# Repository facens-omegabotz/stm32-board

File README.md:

# stm32f446-board → KiCad Project

PCB design of a development board for the STM32f446 MCU

## Schematics

The PDF can be found [here](STM32-udemy.pdf)

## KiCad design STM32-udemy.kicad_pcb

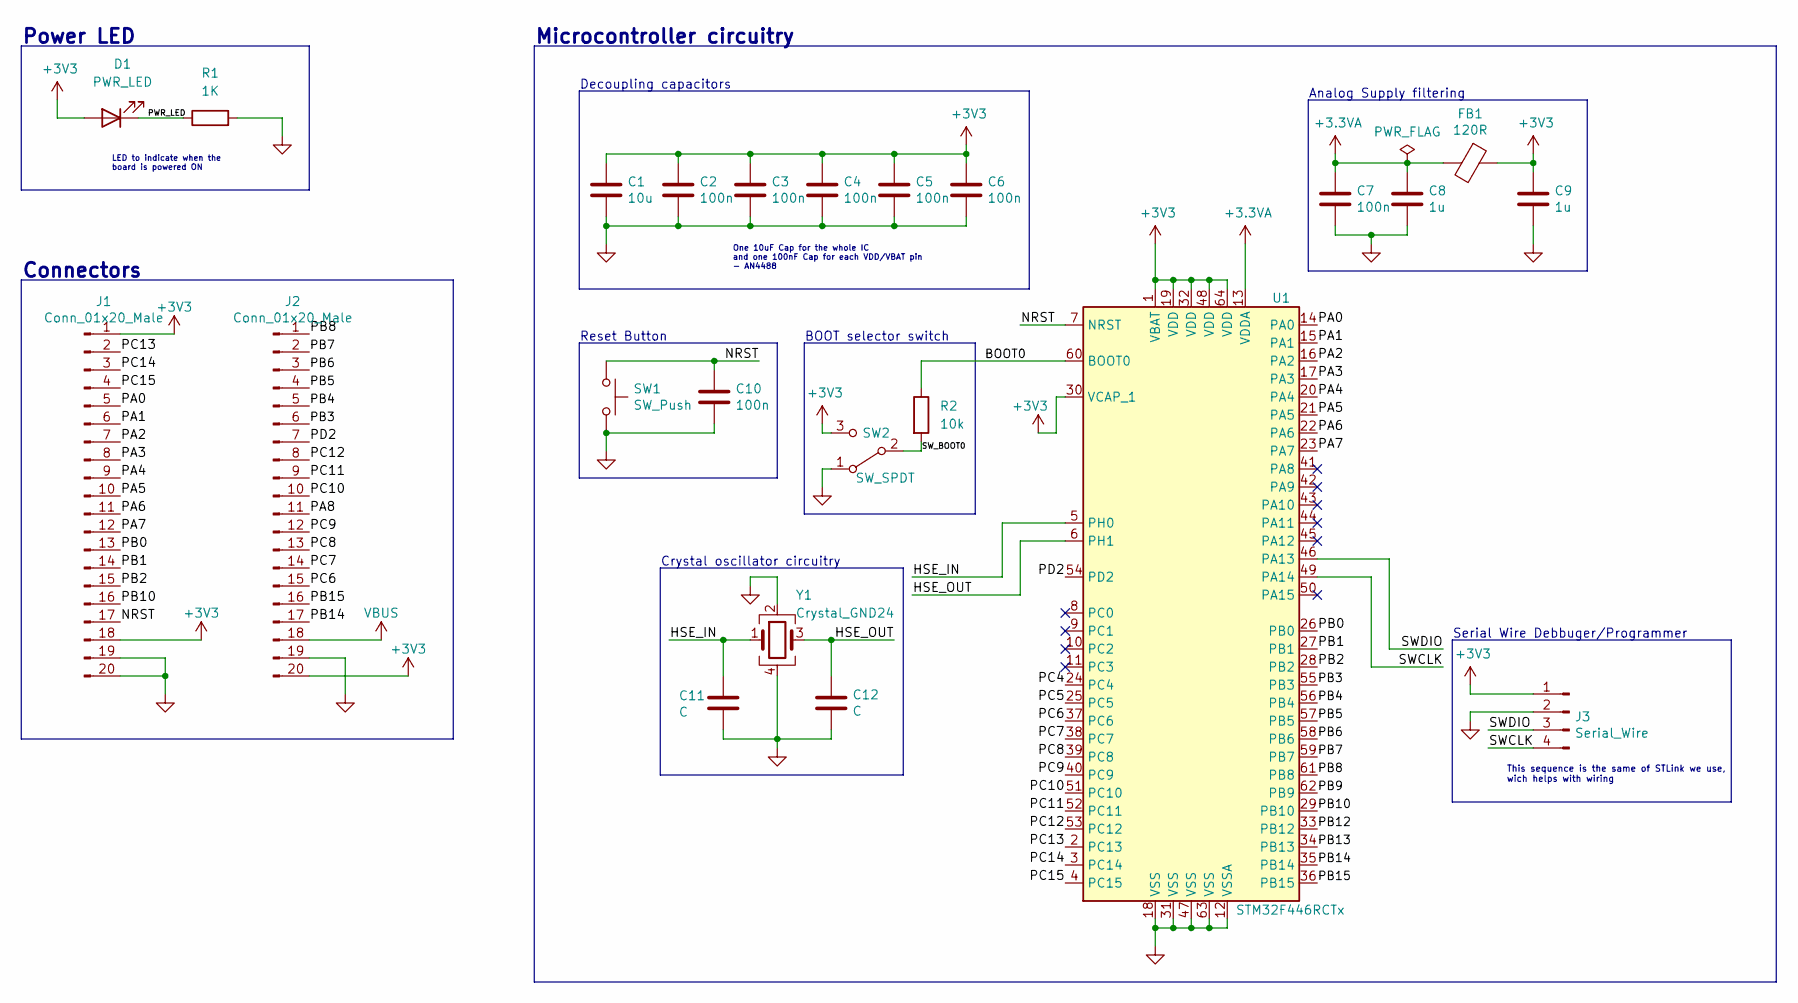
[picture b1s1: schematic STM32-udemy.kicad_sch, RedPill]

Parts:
C1: 10u; C_0805_2012Metric_Pad1.18x1.45mm_HandSolder
C2, C3, C4, C5, C6, C7, C10: 100n; C_0603_1608Metric_Pad1.08x0.95mm_HandSolder
C8, C9: 1u; C_0603_1608Metric_Pad1.08x0.95mm_HandSolder
C11, C12: C; C_0402_1005Metric_Pad0.74x0.62mm_HandSolder
D1: PWR_LED; LED_0603_1608Metric_Pad1.05x0.95mm_HandSolder
FB1: 120R; L_0603_1608Metric_Pad1.05x0.95mm_HandSolder
J1, J2: Conn_01x20_Male; PinHeader_1x20_P2.54mm_Vertical
J3: Serial_Wire; PinHeader_1x04_P2.54mm_Vertical
R1: 1K; R_0603_1608Metric_Pad0.98x0.95mm_HandSolder
R2: 10k; R_0603_1608Metric_Pad0.98x0.95mm_HandSolder
SW1: SW_Push; SW_Push_1P1T_NO_Vertical_Wuerth_434133025816
SW2: SW_SPDT; SW_SPDT_PCM12
U1: STM32F446RCTx; LQFP-64_10x10mm_P0.5mm
Y1: Crystal_GND24; Crystal_SMD_3225-4Pin_3.2x2.5mm

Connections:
+3.3VA: C7.1, C8.1, FB1.2, U1.13 (VDDA)
+3V3: C1.1, C2.1, C3.1, C4.1, C5.1, C6.1, C9.1, D1.2 (A), FB1.1, J1.1, J1.18, J2.20, J3.1, SW2.3 (C), U1.1 (VBAT), U1.19 (VDD), U1.30 (VCAP_1), U1.32 (VDD), U1.48 (VDD), U1.64 (VDD)
/BOOT0: R2.1, U1.60 (BOOT0)
/HSE_IN: C11.1, U1.5 (PH0), Y1.1
/HSE_OUT: C12.1, U1.6 (PH1), Y1.3
/NRST: C10.1, J1.17, SW1.1, U1.7 (NRST)
/PA0: J1.5, U1.14 (PA0)
/PA1: J1.6, U1.15 (PA1)
/PA2: J1.7, U1.16 (PA2)
/PA3: J1.8, U1.17 (PA3)
/PA4: J1.9, U1.20 (PA4)
/PA5: J1.10, U1.21 (PA5)
/PA6: J1.11, U1.22 (PA6)
/PA7: J1.12, U1.23 (PA7)
/PA8: J2.11
/PB0: J1.13, U1.26 (PB0)
/PB1: J1.14, U1.27 (PB1)
/PB2: J1.15, U1.28 (PB2)
/PB3: J2.6, U1.55 (PB3)
/PB4: J2.5, U1.56 (PB4)
/PB5: J2.4, U1.57 (PB5)
/PB6: J2.3, U1.58 (PB6)
/PB7: J2.2, U1.59 (PB7)
/PB8: J2.1, U1.61 (PB8)
/PB9: U1.62 (PB9)
/PB10: J1.16, U1.29 (PB10)
/PB12: U1.33 (PB12)
/PB13: U1.34 (PB13)
/PB14: J2.17, U1.35 (PB14)
/PB15: J2.16, U1.36 (PB15)
/PC4: U1.24 (PC4)
/PC5: U1.25 (PC5)
/PC6: J2.15, U1.37 (PC6)
/PC7: J2.14, U1.38 (PC7)
/PC8: J2.13, U1.39 (PC8)
/PC9: J2.12, U1.40 (PC9)
/PC10: J2.10, U1.51 (PC10)
/PC11: J2.9, U1.52 (PC11)
/PC12: J2.8, U1.53 (PC12)
/PC13: J1.2, U1.2 (PC13)
/PC14: J1.3, U1.3 (PC14)
/PC15: J1.4, U1.4 (PC15)
/PD2: J2.7, U1.54 (PD2)
/PWR_LED: D1.1 (K), R1.1
/SWCLK: J3.4, U1.49 (PA14)
/SWDIO: J3.3, U1.46 (PA13)
/SW_BOOT0: R2.2, SW2.2 (B)
GND: C1.2, C2.2, C3.2, C4.2, C5.2, C6.2, C7.2, C8.2, C9.2, C10.2, C11.2, C12.2, J1.19, J1.20, J2.19, J3.2, R1.2, SW1.2, SW2.1 (A), U1.12 (VSSA), U1.18 (VSS), U1.31 (VSS), U1.47 (VSS), U1.63 (VSS), Y1.2, Y1.4
VBUS: J2.18

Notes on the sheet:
Connectors
Crystal oscillator circuitry
Reset Button
LED to indicate when the board is powered ON
Microcontroller circuitry
This sequence is the same of STLink we use, wich helps with wiring
Power LED
Analog Supply filtering
BOOT selector switch
Serial Wire Debbuger/Programmer
Decoupling capacitors
One 10uF Cap for the whole IC and one 100nF Cap for each VDD/VBAT pin - AN4488

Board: 2 copper layers, 23 parts (12 on the bottom side), 42 nets, no tracks yet.

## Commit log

2022-02-07 Add Schematic file
    First local commit, adding schematic file with:
    - STM32F446RCT6 MCU
    - Decoupling capacitors
2022-02-07 Add pcb and project files
2022-02-08 Add USB and Serial Wire schematic
2022-02-08 Add KiCAD V6 files
2022-02-17 Schematic and basic layout
2022-02-17 Remove components that are not essential
2022-02-20 Initial board layout
